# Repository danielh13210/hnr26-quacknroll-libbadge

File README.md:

# Hack&Roll 2026 "Quack & Roll" hardware badge firmware

This repository contains the firmware source files for the
Hack&Roll 2026 hardware badge to allow the reuse of the badge for other projects.

## License

See the root directory's [LICENSE.md](./LICENSE.md) for more information on how
these materials are licensed.

## Acknowledgements

This Hack&Roll 2026 hardware badge would not have been possible without the
following people:

- **Terence** Chan Zun Mun ([@Hackin7](https://github.com/Hackin7)), for his
  invaluable knowledge and guidance in PCB design and hardware badge
  development, as well as liaising with Espressif Systems
- Tan **Le Yew** ([@itsme-zeix](https://github.com/itsme-zeix)), for helping out
  with development and troubleshooting of the NFC controller badge
- Lim **Yik Jin** ([@yikjin](https://github.com/yikjin)), for developing the
  hardware badges
- Park **Youngseo** ([@youngseopark05](https://github.com/youngseopark05)), for
  creating the artwork used for this hardware badge
- Koh Chan Hong, **Ravern** ([@ravern](https://github.com/ravern)), for liaising
  with Espressif Systems
- Tan Rongwen, **Daren** ([@darentanrw](https://github.com/darentanrw)), for
  liaising with Espressif Systems
- Everyone in [NUS Hackers](https://www.nushackers.org/) for making Hack&Roll
  2026 a reality!

The ESP32-C3-WROOM-02-N4 module in this hardware badge is also sponsored by
[Espressif Systems](https://www.espressif.com/), the manufacturers of the
widely-used ESP32 chips.

## Install

To install the firmware, run ./install.sh

A module ```libbadge``` will be created, to use the LEDs, speaker, and buttons.

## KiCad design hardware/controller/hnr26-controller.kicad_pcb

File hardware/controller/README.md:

# HnR'26 hardware badge: NFC controller hardware source files

This directory contains the [KiCad](https://www.kicad.org/) 9 hardware source
files for the Hack&Roll 2026 hardware badge NFC controller.

This NFC controller is used to track participant statistics during food
collection by using NFC communication to scan the participant badges. It can be
extended on to track event statistics during Hack&Roll 2026 as well.

## Manufacturing

We used [JLCPCB manufacturing services](https://jlcpcb.com/) for the hardware
badges. To help with generating JLCPCB-compatible files, we used the open source
[KiCad JLCPCB tools](https://github.com/bouni/kicad-jlcpcb-tools) plugin.

## License

The hardware source files in this directory are open-sourced, licensed under
CERN-OHL-P-2.0. See [LICENSE.md](./LICENSE.md) for the full license text.

## Acknowledgements

This Hack&Roll 2026 NFC controller hardware badge would not have been possible
without the following people:

- **Terence** Chan Zun Mun ([@Hackin7](https://github.com/Hackin7)), for his
  invaluable knowledge and guidance in PCB design and hardware badge
  development, as well as liaising with Espressif Systems
- Tan **Le Yew** ([@itsme-zeix](https://github.com/itsme-zeix)), for helping out
  with development and troubleshooting of the NFC controller badge
- Lim **Yik Jin** ([@yikjin](https://github.com/yikjin)), for developing the
  hardware badges
- Park **Youngseo** ([@youngseopark05](https://github.com/youngseopark05)), for
  creating the artwork used for this hardware badge
- Koh Chan Hong, **Ravern** ([@ravern](https://github.com/ravern)), for liaising
  with Espressif Systems
- Tan Rongwen, **Daren** ([@darentanrw](https://github.com/darentanrw)), for
  liaising with Espressif Systems
- Everyone in [NUS Hackers](https://www.nushackers.org/) for making Hack&Roll
  2026 a reality!

The ESP32-C3-WROOM-02-N4 module in the main hardware badge is also sponsored by
[Espressif Systems](https://www.espressif.com/), the manufacturers of the
widely-used ESP32 chips.

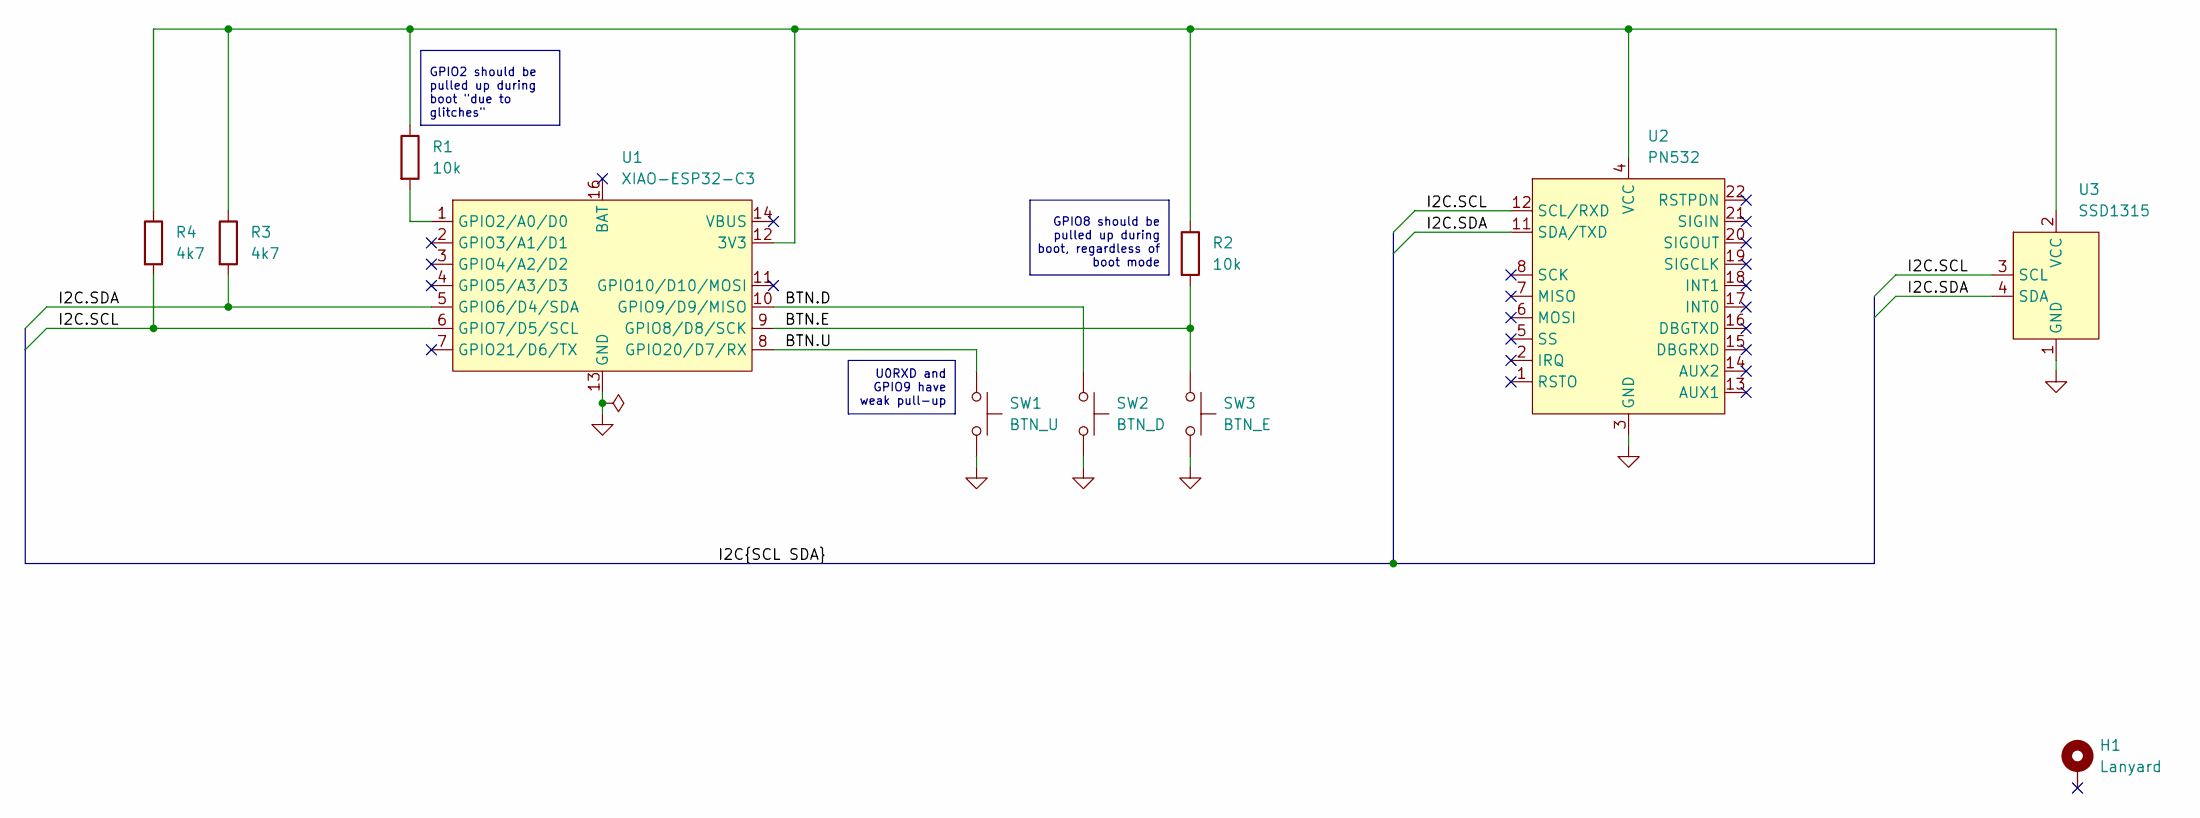
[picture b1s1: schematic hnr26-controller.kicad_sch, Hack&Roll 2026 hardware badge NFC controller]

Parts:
H1: Lanyard; MountingHole_3.2mm_M3_Pad_Via
R1, R2: 10k; R_Axial_DIN0207_L6.3mm_D2.5mm_P10.16mm_Horizontal
R3, R4: 4k7; R_0805_2012Metric_Pad1.20x1.40mm_HandSolder
SW1: BTN_U; SW_PUSH_6mm
SW2: BTN_D; SW_PUSH_6mm
SW3: BTN_E; SW_PUSH_6mm
U1: XIAO-ESP32-C3; MCU_Seeed_ESP32C3
U2: PN532; NFC_PN532_Module
U3: SSD1315; OLED_SSD1315_I2C_0.96in

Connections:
/BTN.D: SW2.1, U1.10 (GPIO9/D9/MISO)
/BTN.E: R2.2, SW3.1, U1.9 (GPIO8/D8/SCK)
/BTN.U: SW1.1, U1.8 (GPIO20/D7/RX)
/I2C.SCL: R4.2, U1.6 (GPIO7/D5/SCL), U2.12 (SCL/RXD), U3.3 (SCL)
/I2C.SDA: R3.2, U1.5 (GPIO6/D4/SDA), U2.11 (SDA/TXD), U3.4 (SDA)
GND: SW1.2, SW2.2, SW3.2, U1.13 (GND), U1.15 (GND), U1.17 (GND), U2.3 (GND), U2.9 (GND), U3.1 (GND)
unnamed: R1.2, U1.1 (GPIO2/A0/D0)
VCC: R1.1, R2.1, R3.1, R4.1, U1.12 (3V3), U2.4 (VCC), U2.10 (VCC), U3.2 (VCC)

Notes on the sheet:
U0RXD and GPIO9 have weak pull-up
GPIO8 should be pulled up during boot, regardless of boot mode
GPIO2 should be pulled up during boot "due to glitches"

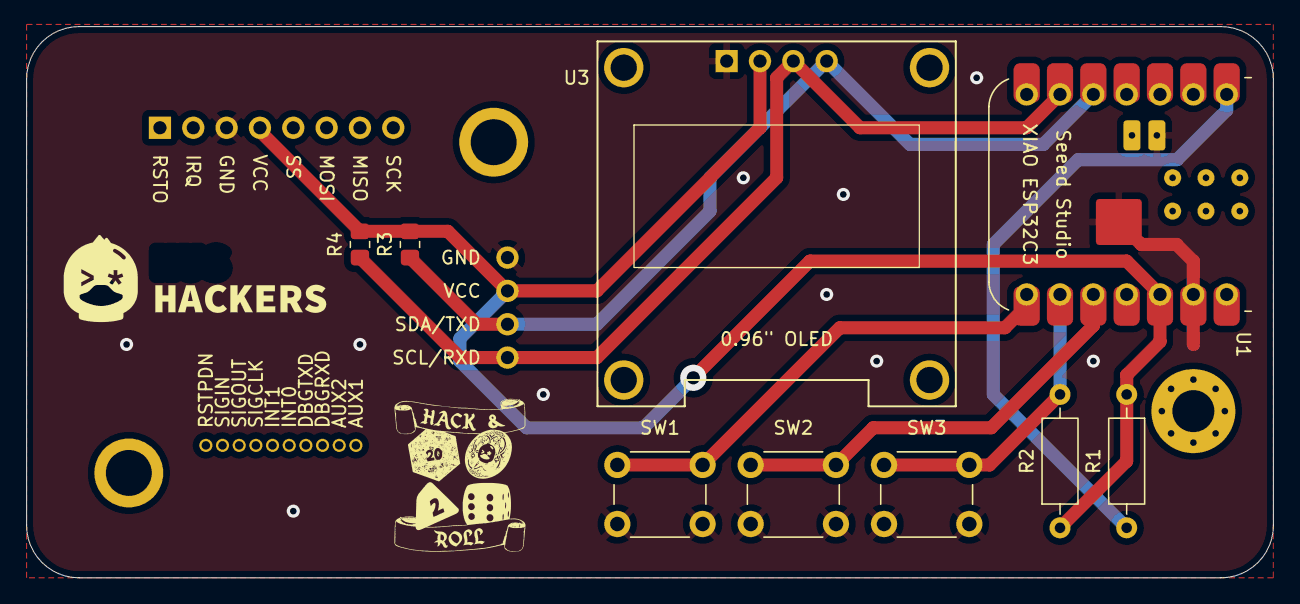
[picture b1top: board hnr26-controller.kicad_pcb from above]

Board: 2 copper layers, 95.0 x 42.0 mm, 11 parts (1 on the bottom side), 8 nets.

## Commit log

2026-01-23 chore: add NFC controller files
    Add NFC controller hardware and firmware files.
    Update README and LICENSE texts for various components.
2026-02-10 Remove art
2026-02-10 Delete controller (NFC programmer) firmware
    This repo is for the badge not the NFC programmer
2026-02-10 Only leave the libraries
    This repo is library only. For reusing the badge.
2026-02-10 Move files
2026-02-10 Add a loader script
2026-02-10 Move to /firmware
2026-02-10 Add an install script
2026-02-11 Don't inject to builtins
    Expose as singleton instead
